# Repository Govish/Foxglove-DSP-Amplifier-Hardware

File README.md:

# Foxglove DSP Amplifier
 Design data for a DSP-based guitar effects processor

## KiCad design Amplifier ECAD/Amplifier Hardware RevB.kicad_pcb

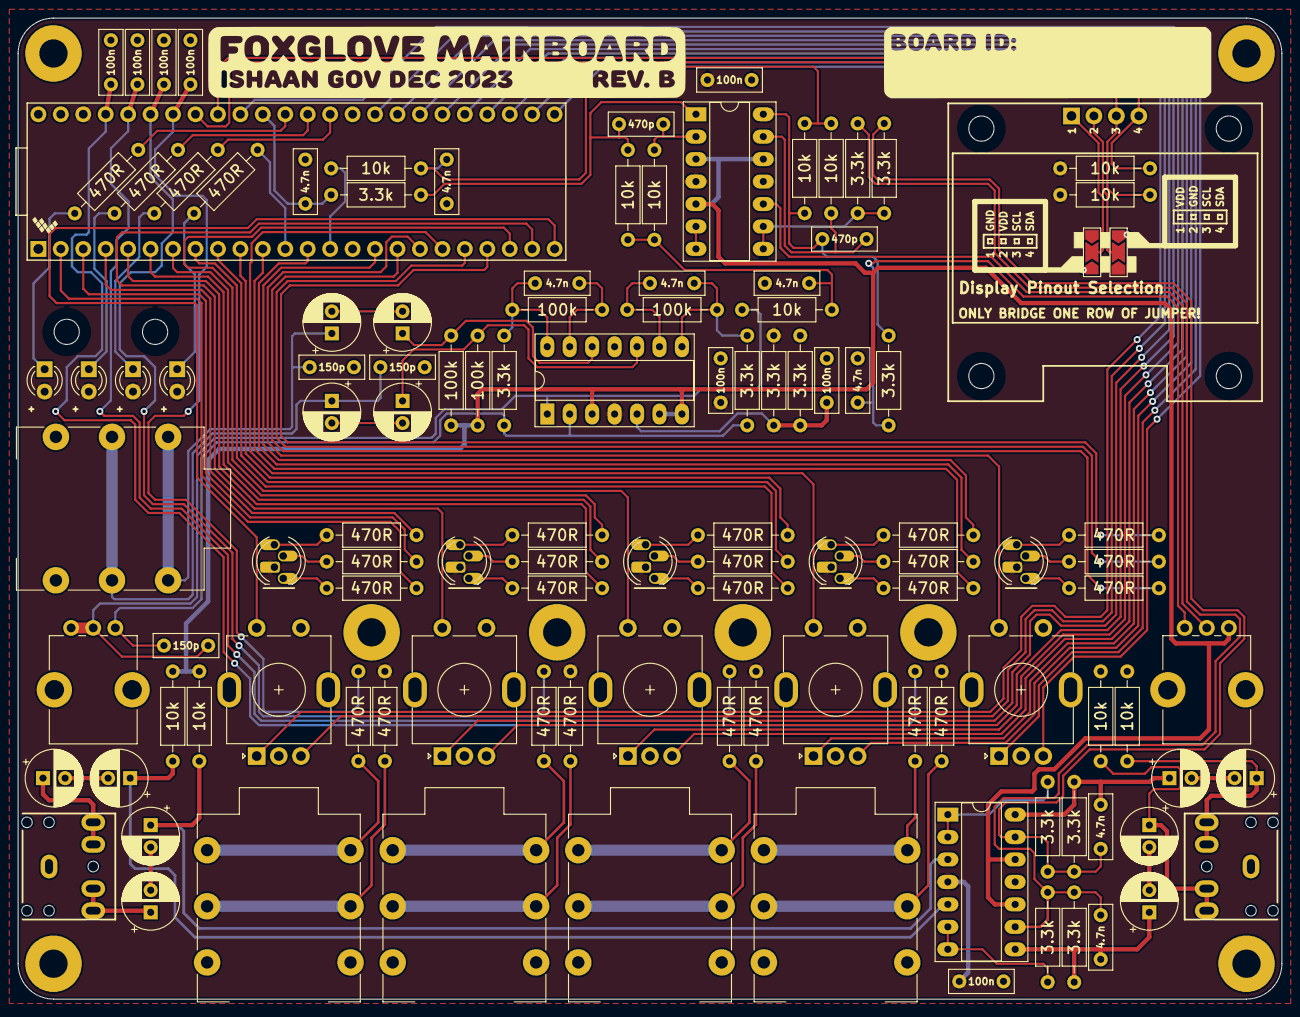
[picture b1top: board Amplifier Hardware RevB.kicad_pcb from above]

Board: 2 copper layers, 143.0 x 111.0 mm, 132 parts (0 on the bottom side), 113 nets.

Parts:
C1, C2, C3, C4, C7, C8, C9, C10, C16, C17, C18, C19: 100u; CP_KEMET_ESY
C5, C6, C13: 150p; C_KEMET_C317
C11, C12, C14, C15, C20, C22, C23, C25: 4.7n; C_KEMET_C322
C21, C24: 470p; C_KEMET_C317
C26, C27, C28, C29, C30, C31, C32, C33: 100n; C_KEMET_C317
D1, D2, D3, D4, D9: RGB; LED_D5.0mm-4_RGB
D5: RED; LED_D3.0mm_Clear
D6, D7, D8: YELLOW; LED_D3.0mm_Clear
H1, H2, H3, H4, H5, H6, H7, H8: M3; MountingHole_3.2mm_M3_Pad
H9, H10, H11, H12, H13, H14: M2.6; MountingHole_2.9mm_5.5mm_Ring
J1, J7: 3.5mm TRS; PJ-307
J2, J3, J4, J5, J6: NMJ6HFD2; Jack_6.35mm_Neutrik_NMJ6HFD2_Horizontal
JP1, JP2: SolderJumper_3_Bridged12; SolderJumper-3_P2.0mm_Open_TrianglePad1.0x1.5mm
R1, R2, R15, R16, R17, R18, R19, R21, R22, R23, R54, R55: 10k; R_Axial_DIN0207_L6.3mm_D2.5mm_P10.16mm_Horizontal
R3, R4, R5, R6: 100k; R_Axial_DIN0207_L6.3mm_D2.5mm_P10.16mm_Horizontal
R7, R8, R9, R10, R11, R12, R13, R14, R20, R24, R25, R26: 3.3k; R_Axial_DIN0207_L6.3mm_D2.5mm_P10.16mm_Horizontal
R27, R28, R29, R30, R31, R32, R33, R34, R35, R36, R37, R38, R39, R40, R41, R42, R43, R44, R45, R46, R47, R48, R49, R50, R51, R52, R53: 470R; R_Axial_DIN0207_L6.3mm_D2.5mm_P10.16mm_Horizontal
RV1, RV2: 100k Log; Potentiometer_Bourns_PTV09A-1_Single_Vertical
SW1, SW2, SW3, SW4, SW5: EC11; RotaryEncoder_Alps_EC11E-Switch_Vertical_H20mm
U1, U2, U3: MCP6004; DIP-14_W7.62mm_Socket_LongPads_IC
U4: Teensy 4.1; Teensy_4_1_Basic_Socket
U5: SH1106; SH1106_LCD_MODULE

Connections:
+3.3V: C26.1, C28.1, C29.1, D1.2 (A), D2.2 (A), D3.2 (A), D4.2 (A), D5.2 (A), D6.2 (A), D7.2 (A), D8.2 (A), D9.2 (A), JP1.1 (A), JP2.3 (B), R25.2, R30.1, R35.1, R40.1, R45.1, R54.1, R55.1, U1.4 (V+), U2.4 (V+), U3.4 (V+), U4.46 (3V3)
/Anti-Aliasing Filter/AMP_INST_IN: C13.2, R17.1, RV1.2, RV1.3, U1.1
/Anti-Aliasing Filter/FILT_INST_IN: C22.1, R20.2, U4.38 ((A2)PIN_16)
/BIAS: R1.1, R2.1, R3.1, R4.1, RV2.1, U1.3 (+), U1.6 (-), U1.7, U2.10 (+), U2.12 (+), U3.3 (+), U3.5 (+), U3.12 (+)
/Effect Channel 1/ENC_A: SW1.A, U4.25 (~PIN_33)
/Effect Channel 1/ENC_B: SW1.B, U4.26 (PIN_34)
/Effect Channel 1/ENC_SW: SW1.S2, U4.24 (PIN_32)
/Effect Channel 1/EXP_IN: C30.1, R31.1, U4.42 ((A6)PIN_20)
/Effect Channel 1/EXP_PWR: J3.R, J3.RN, R30.2
/Effect Channel 1/EXP_SIG: J3.T, J3.TN, R31.2
/Effect Channel 1/LED_B: R29.1, U4.3 (~PIN_1)
/Effect Channel 1/LED_G: R28.1, U4.4 (~PIN_2)
/Effect Channel 1/LED_R: R27.1, U4.2 (~PIN_0)
/Effect Channel 2/ENC_A: SW2.A, U4.27 (PIN_35)
/Effect Channel 2/ENC_B: SW2.B, U4.28 (~PIN_36)
/Effect Channel 2/ENC_SW: SW2.S2, U4.23 (PIN_31)
/Effect Channel 2/EXP_IN: C31.1, R36.1, U4.43 ((A7)PIN_21)
/Effect Channel 2/EXP_PWR: J4.R, J4.RN, R35.2
/Effect Channel 2/EXP_SIG: J4.T, J4.TN, R36.2
/Effect Channel 2/LED_B: R34.1, U4.6 (~PIN_4)
/Effect Channel 2/LED_G: R33.1, U4.7 (~PIN_5)
/Effect Channel 2/LED_R: R32.1, U4.5 (~PIN_3)
/Effect Channel 3/ENC_A: SW3.A, U4.29 (~PIN_37)
/Effect Channel 3/ENC_B: SW3.B, U4.30 ((A14)PIN_38)
/Effect Channel 3/ENC_SW: SW3.S2, U4.22 (PIN_30)
/Effect Channel 3/EXP_IN: C32.1, R41.1, U4.44 ((A8)PIN_22)
/Effect Channel 3/EXP_PWR: J5.R, J5.RN, R40.2
/Effect Channel 3/EXP_SIG: J5.T, J5.TN, R41.2
/Effect Channel 3/LED_B: R39.1, U4.9 (~PIN_7)
/Effect Channel 3/LED_G: R38.1, U4.10 (~PIN_8)
/Effect Channel 3/LED_R: R37.1, U4.8 (~PIN_6)
/Effect Channel 4/ENC_A: SW4.A, U4.31 ((A15)PIN_39)
/Effect Channel 4/ENC_B: SW4.B, U4.32 ((A16)PIN_40)
/Effect Channel 4/ENC_SW: SW4.S2, U4.19 (PIN_27(A13))
/Effect Channel 4/EXP_IN: C33.1, R46.1, U4.45 ((A9)PIN_23)
/Effect Channel 4/EXP_PWR: J6.R, J6.RN, R45.2
/Effect Channel 4/EXP_SIG: J6.T, J6.TN, R46.2
/Effect Channel 4/LED_B: R44.1, U4.13 (~PIN_11)
/Effect Channel 4/LED_G: R43.1, U4.16 (~PIN_24(A10))
/Effect Channel 4/LED_R: R42.1, U4.11 (~PIN_9)
/Instrument In/INST_IN_L: C5.2, C7.1, J2.T, J2.TN
/Instrument In/INST_IN_R: C6.2, C8.1, J2.R, J2.RN
/Line In/BUF_LINE_IN_L: R9.1, U2.1, U2.2 (-)
/Line In/BUF_LINE_IN_R: R12.1, U2.6 (-), U2.7
/Line In/LINE_IN_L: C1.1, J1.T, J1.TN
/Line In/LINE_IN_R: C2.1, J1.R, J1.RN
/MCU/EFFECT_RAW: R21.1, U4.14 (~PIN_12)
/MCU/ENC_A_UI: SW5.A, U4.33 ((A17)PIN_41)
/MCU/ENC_B_UI: SW5.B, U4.39 ((A3)PIN_17)
/MCU/ENC_SW_UI: SW5.S2, U4.18 (PIN_26(A12))
/MCU/LED_B_UI: R49.1, U4.20 (~PIN_28)
/MCU/LED_G_UI: R48.1, U4.21 (~PIN_29)
/MCU/LED_R_UI: R47.1, U4.17 (~PIN_25(A11))
/MCU/LEVEL_0: R50.1, U4.37 (~(A1)PIN_15)
/MCU/LEVEL_1: R51.1, U4.36 (~(A0)PIN_14)
/MCU/LEVEL_2: R52.1, U4.35 (~PIN_13)
/MCU/LEVEL_3: R53.1, U4.12 (~PIN_10)
/MCU/SCL: R54.2, U4.41 ((A5)PIN_19), U5.3 (SCL)
/MCU/SDA: R55.2, U4.40 ((A4)PIN_18), U5.4 (SDA)
/Reconstruction Filter/EFFECT_RECON: C25.1, R24.2, RV2.3
/Volume_Mixing_Output/LINE_OUT_L: C18.1, J7.T, J7.TN, R15.2
/Volume_Mixing_Output/LINE_OUT_R: C19.1, J7.R, J7.RN, R16.2
GND: C5.1, C6.1, C20.2, C22.2, C23.2, C25.2, C26.2, C27.2, C28.2, C29.2, C30.2, C31.2, C32.2, C33.2, H1.1, H2.1, H3.1, H4.1, H5.1, H6.1, H7.1, H8.1, J1.S, J2.S, J2.SN, J3.S, J3.SN, J4.S, J4.SN, J5.S, J5.SN, J6.S, J6.SN, J7.S, JP1.3 (B), JP2.1 (A), R15.1, R16.1, R26.1, RV1.MNT, RV2.MNT, SW1.C, SW1.MP, SW1.S1, SW2.C, SW2.MP, SW2.S1, SW3.C, SW3.MP, SW3.S1, SW4.C, SW4.MP, SW4.S1, SW5.C, SW5.MP, SW5.S1, U1.11 (V-), U2.11 (V-), U3.11 (V-), U4.1 (GND), U4.34 (GND), U4.47 (GND)
unnamed: C1.2, C3.2
unnamed: C2.2, C4.2
unnamed: C7.2, C9.2
unnamed: C8.2, C10.2
unnamed: C11.2, R5.2, R7.1, U1.14
unnamed: C12.2, R6.2, R8.1, U1.8
unnamed: C14.2, C16.1, R13.2, U2.14
unnamed: C15.2, C17.1, R14.2, U2.8
unnamed: C16.2, C18.2
unnamed: C17.2, C19.2
unnamed: C20.1, R17.2, R18.1, R19.1
unnamed: C21.1, R18.2, R20.1, U3.1
unnamed: C23.1, R21.2, R22.1, R23.1
unnamed: C24.1, R22.2, R24.1, U3.14
unnamed: D1.3 (BK), R29.2
unnamed: D1.4 (GK), R28.2
unnamed: D1.1 (RK), R27.2
unnamed: D2.3 (BK), R34.2
unnamed: D2.4 (GK), R33.2
unnamed: D2.1 (RK), R32.2
unnamed: D3.3 (BK), R39.2
unnamed: D3.4 (GK), R38.2
unnamed: D3.1 (RK), R37.2
unnamed: D4.3 (BK), R44.2
unnamed: D4.4 (GK), R43.2
unnamed: D4.1 (RK), R42.2
unnamed: D5.1 (K), R50.2
unnamed: D6.1 (K), R51.2
unnamed: D7.1 (K), R52.2
unnamed: D8.1 (K), R53.2
unnamed: D9.3 (BK), R49.2
unnamed: D9.4 (GK), R48.2
unnamed: D9.1 (RK), R47.2
unnamed: JP1.2 (C), U5.1 (VDD)
unnamed: JP2.2 (C), U5.2 (GND)
unnamed: C13.1, R7.2, R8.2, RV1.1, U1.2 (-)
unnamed: C27.1, R25.1, R26.2, U1.5 (+)
unnamed: C10.1, R4.2, U1.10 (+)
unnamed: C12.1, R6.1, U1.9 (-)
unnamed: C9.1, R3.2, U1.12 (+)
unnamed: C11.1, R5.1, U1.13 (-)
unnamed: C3.1, R1.2, U2.3 (+)
unnamed: C4.1, R2.2, U2.5 (+)
unnamed: C15.1, R11.2, R12.2, R14.1, U2.9 (-)
unnamed: C14.1, R9.2, R10.2, R13.1, U2.13 (-)
unnamed: C21.2, R19.2, U3.2 (-)
unnamed: U3.6 (-), U3.7
unnamed: RV2.2, U3.10 (+)
unnamed: R10.1, R11.1, U3.8, U3.9 (-)
unnamed: C24.2, R23.2, U3.13 (-)

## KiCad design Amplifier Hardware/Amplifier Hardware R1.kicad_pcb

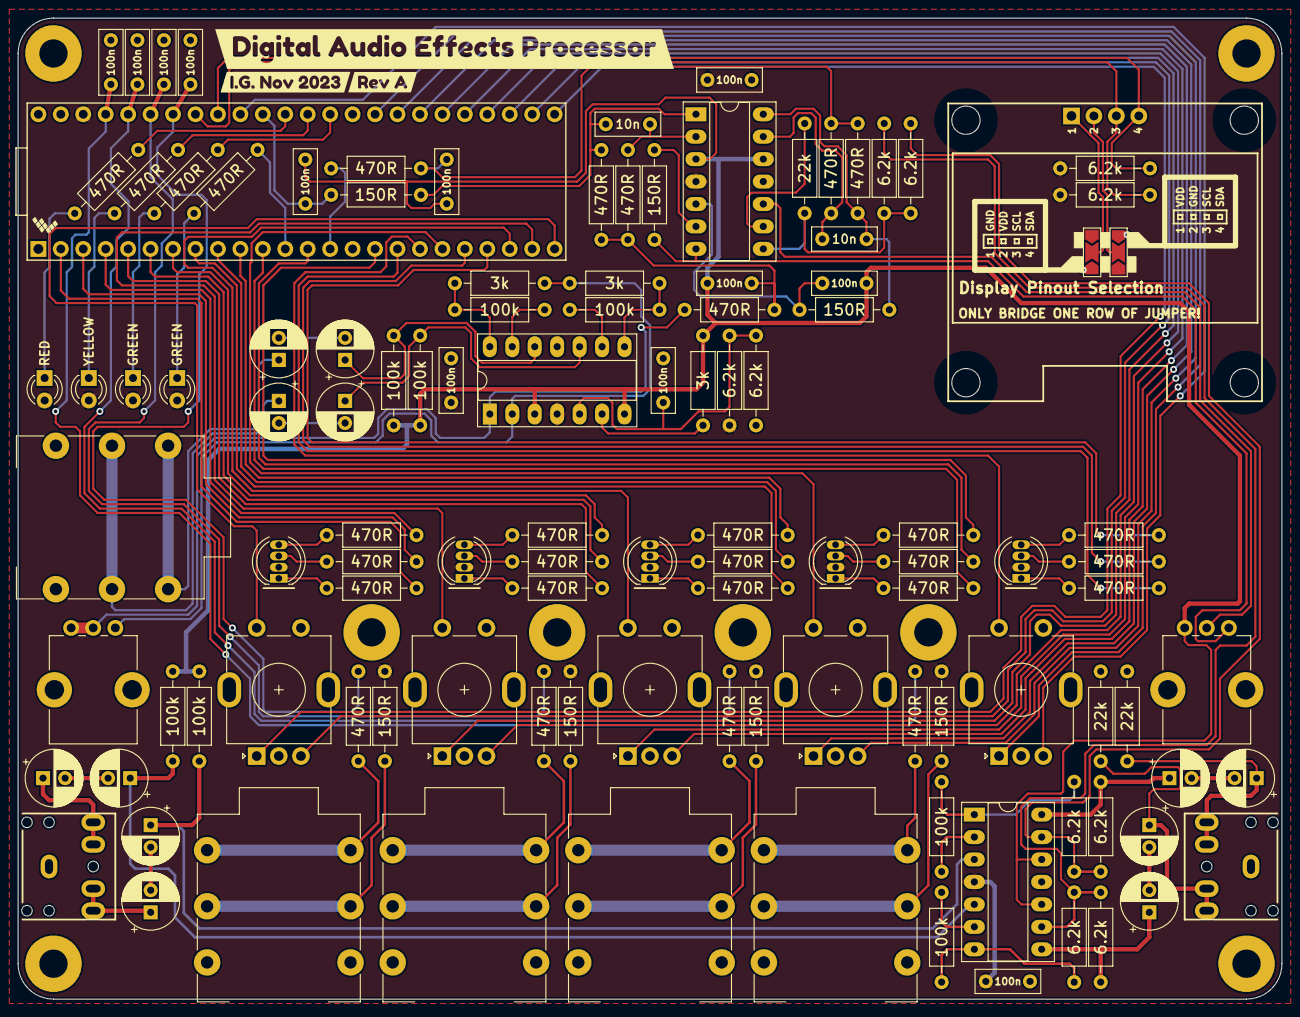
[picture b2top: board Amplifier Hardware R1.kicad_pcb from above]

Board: 2 copper layers, 143.0 x 111.0 mm, 127 parts (0 on the bottom side), 118 nets.

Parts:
C1, C2, C3, C4, C5, C6, C7, C8, C9, C10, C11, C12: 100u; CP_Radial_D6.3mm_H12.5_P2.50mm
C13, C15, C16, C18, C19, C20, C21, C22, C23, C24, C25, C26: 100n; C_Rect_L7.2mm_W2.5mm_H6.6mm_P5.00mm_MODIFIED
C14, C17: 10n; C_Rect_L7.2mm_W2.5mm_H6.6mm_P5.00mm_MODIFIED
D1, D2, D3, D4, D9: QBL8RGB60D0-2897; LED_D5.0mm-4_RGB
D5: RED; LED_D3.0mm_Clear
D6: YELLOW; LED_D3.0mm_Clear
D7, D8: GREEN; LED_D3.0mm_Clear
H1, H2, H3, H4, H5, H6, H7, H8: M3; MountingHole_3.2mm_M3_Pad
J1, J7: SJ1-3525N; PJ-307
J2, J3, J4, J5, J6: NMJ6HFD2; Jack_6.35mm_Neutrik_NMJ6HFD2_Horizontal
JP1, JP2: SolderJumper_3_Bridged12; SolderJumper-3_P2.0mm_Open_TrianglePad1.0x1.5mm
R1, R2, R3, R4, R15, R16, R17, R18: 100k; R_Axial_DIN0207_L6.3mm_D2.5mm_P10.16mm_Horizontal
R5, R24, R28, R35, R40, R45, R50: 150R; R_Axial_DIN0207_L6.3mm_D2.5mm_P10.16mm_Horizontal
R6, R13, R14: 22k; R_Axial_DIN0207_L6.3mm_D2.5mm_P10.16mm_Horizontal
R7, R8, R9, R10, R11, R12, R29, R30, R59, R60: 6k2; R_Axial_DIN0207_L6.3mm_D2.5mm_P10.16mm_Horizontal
R19, R20, R31: 3k; R_Axial_DIN0207_L6.3mm_D2.5mm_P10.16mm_Horizontal
R21, R22, R23, R25, R26, R27, R32, R33, R34, R36, R37, R38, R39, R41, R42, R43, R44, R46, R47, R48, R49, R51, R52, R53, R54, R55, R56, R57, R58: 470R; R_Axial_DIN0207_L6.3mm_D2.5mm_P10.16mm_Horizontal
RV1, RV2: 100k Log; Potentiometer_Bourns_PTV09A-1_Single_Vertical
SW1, SW2, SW3, SW4, SW5: EC11; RotaryEncoder_Alps_EC11E-Switch_Vertical_H20mm
U1, U2, U3: MCP6004; DIP-14_W7.62mm_Socket_LongPads_IC
U4: Teensy 4.1; Teensy_4_1_Basic_Socket
U5: SH1106; SH1106_LCD_MODULE
kibuzzard-6562A21D: G***; kibuzzard-6562A21D
kibuzzard-6562A25D: G***; kibuzzard-6562A25D
kibuzzard-6562EE33: G***; kibuzzard-6562EE33

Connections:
+3.3V: C19.1, C21.1, C22.1, D1.2 (A), D2.2 (A), D3.2 (A), D4.2 (A), D5.2 (A), D6.2 (A), D7.2 (A), D8.2 (A), D9.2 (A), JP1.1 (A), JP2.3 (B), R29.1, R35.1, R40.1, R45.1, R50.1, R59.2, R60.2, U1.4 (V+), U2.4 (V+), U3.4 (V+), U4.46 (3V3)
/Anti-Aliasing Filter/AMP_INST_IN: R21.1, RV2.2, RV2.3, U3.1
/Anti-Aliasing Filter/FILT_INST_IN: C15.1, R24.2, U4.38 ((A2)PIN_16)
/BIAS: C13.2, C15.2, C16.2, C18.2, R1.1, R2.1, R15.1, R16.1, R31.2, RV1.3, U1.10 (+), U1.12 (+), U2.3 (+), U2.12 (+), U3.3 (+), U3.7
/Effect Channel 1/ENC_A: SW4.A, U4.25 (~PIN_33)
/Effect Channel 1/ENC_B: SW4.B, U4.26 (PIN_34)
/Effect Channel 1/ENC_SW: SW4.S2, U4.24 (PIN_32)
/Effect Channel 1/EXP_IN: C26.1, R51.1, U4.42 ((A6)PIN_20)
/Effect Channel 1/EXP_PWR: J3.R, J3.RN, R50.2
/Effect Channel 1/EXP_SIG: J3.T, J3.TN, R51.2
/Effect Channel 1/LED_B: R49.1, U4.3 (~PIN_1)
/Effect Channel 1/LED_G: R48.1, U4.4 (~PIN_2)
/Effect Channel 1/LED_R: R47.1, U4.2 (~PIN_0)
/Effect Channel 2/ENC_A: SW2.A, U4.27 (PIN_35)
/Effect Channel 2/ENC_B: SW2.B, U4.28 (~PIN_36)
/Effect Channel 2/ENC_SW: SW2.S2, U4.23 (PIN_31)
/Effect Channel 2/EXP_IN: C24.1, R41.1, U4.43 ((A7)PIN_21)
/Effect Channel 2/EXP_PWR: J4.R, J4.RN, R40.2
/Effect Channel 2/EXP_SIG: J4.T, J4.TN, R41.2
/Effect Channel 2/LED_B: R39.1, U4.6 (~PIN_4)
/Effect Channel 2/LED_G: R38.1, U4.7 (~PIN_5)
/Effect Channel 2/LED_R: R37.1, U4.5 (~PIN_3)
/Effect Channel 3/ENC_A: SW1.A, U4.29 (~PIN_37)
/Effect Channel 3/ENC_B: SW1.B, U4.30 ((A14)PIN_38)
/Effect Channel 3/ENC_SW: SW1.S2, U4.22 (PIN_30)
/Effect Channel 3/EXP_IN: C23.1, R36.1, U4.44 ((A8)PIN_22)
/Effect Channel 3/EXP_PWR: J5.R, J5.RN, R35.2
/Effect Channel 3/EXP_SIG: J5.T, J5.TN, R36.2
/Effect Channel 3/LED_B: R34.1, U4.9 (~PIN_7)
/Effect Channel 3/LED_G: R33.1, U4.10 (~PIN_8)
/Effect Channel 3/LED_R: R32.1, U4.8 (~PIN_6)
/Effect Channel 4/ENC_A: SW3.A, U4.31 ((A15)PIN_39)
/Effect Channel 4/ENC_B: SW3.B, U4.32 ((A16)PIN_40)
/Effect Channel 4/ENC_SW: SW3.S2, U4.19 (PIN_27(A13))
/Effect Channel 4/EXP_IN: C25.1, R46.1, U4.45 ((A9)PIN_23)
/Effect Channel 4/EXP_PWR: J6.R, J6.RN, R45.2
/Effect Channel 4/EXP_SIG: J6.T, J6.TN, R46.2
/Effect Channel 4/LED_B: R44.1, U4.13 (~PIN_11)
/Effect Channel 4/LED_G: R43.1, U4.16 (~PIN_24(A10))
/Effect Channel 4/LED_R: R42.1, U4.11 (~PIN_9)
/Instrument In/INST_IN_L: C9.1, J2.T, J2.TN
/Instrument In/INST_IN_R: C10.1, J2.R, J2.RN
/Line In/BUF_LINE_IN_L: R3.2, R8.1, U1.1
/Line In/BUF_LINE_IN_R: R4.2, R10.1, U1.7
/Line In/LINE_IN_L: C1.1, J1.T, J1.TN
/Line In/LINE_IN_R: C2.1, J1.R, J1.RN
/MCU/EFFECT_RAW: R25.1, U4.14 (~PIN_12)
/MCU/ENC_A_UI: SW5.A, U4.33 ((A17)PIN_41)
/MCU/ENC_B_UI: SW5.B, U4.39 ((A3)PIN_17)
/MCU/ENC_SW_UI: SW5.S2, U4.18 (PIN_26(A12))
/MCU/LED_B_UI: R54.1, U4.20 (~PIN_28)
/MCU/LED_G_UI: R53.1, U4.21 (~PIN_29)
/MCU/LED_R_UI: R52.1, U4.17 (~PIN_25(A11))
/MCU/LEVEL_0: R55.1, U4.37 (~(A1)PIN_15)
/MCU/LEVEL_1: R56.1, U4.36 (~(A0)PIN_14)
/MCU/LEVEL_2: R57.1, U4.35 (~PIN_13)
/MCU/LEVEL_3: R58.1, U4.12 (~PIN_10)
/MCU/SCL: R59.1, U4.41 ((A5)PIN_19), U5.3 (SCL)
/MCU/SDA: R60.1, U4.40 ((A4)PIN_18), U5.4 (SDA)
/Reconstruction Filter/EFFECT_RECON: C18.1, R28.2, U2.5 (+)
/Volume_Mixing_Output/LINE_OUT_L: C7.1, J7.T, J7.TN, R13.2
/Volume_Mixing_Output/LINE_OUT_R: C8.1, J7.R, J7.RN, R14.2
GND: C19.2, C20.2, C21.2, C22.2, C23.2, C24.2, C25.2, C26.2, H1.1, H2.1, H3.1, H4.1, H5.1, H6.1, H7.1, H8.1, J1.S, J2.S, J2.SN, J3.S, J3.SN, J4.S, J4.SN, J5.S, J5.SN, J6.S, J6.SN, J7.S, JP1.3 (B), JP2.1 (A), R13.1, R14.1, R30.2, RV1.MNT, RV2.MNT, SW1.C, SW1.MP, SW1.S1, SW2.C, SW2.MP, SW2.S1, SW3.C, SW3.MP, SW3.S1, SW4.C, SW4.MP, SW4.S1, SW5.C, SW5.MP, SW5.S1, U1.11 (V-), U2.11 (V-), U3.11 (V-), U4.1 (GND), U4.34 (GND), U4.47 (GND)
unnamed: C1.2, C3.2
unnamed: C2.2, C4.2
unnamed: C5.1, R11.2, U1.14
unnamed: C5.2, C7.2
unnamed: C6.1, R12.2, U1.8
unnamed: C6.2, C8.2
unnamed: C10.2, C12.2
unnamed: C9.2, C11.2
unnamed: C13.1, R21.2, R22.1, R23.1
unnamed: C14.1, R22.2, R24.1, U2.1
unnamed: C16.1, R25.2, R26.1, R27.1
unnamed: C17.1, R26.2, R28.1, U2.14
unnamed: D1.3 (BK), R34.2
unnamed: D1.4 (GK), R33.2
unnamed: D1.1 (RK), R32.2
unnamed: D2.3 (BK), R39.2
unnamed: D2.4 (GK), R38.2
unnamed: D2.1 (RK), R37.2
unnamed: D3.3 (BK), R44.2
unnamed: D3.4 (GK), R43.2
unnamed: D3.1 (RK), R42.2
unnamed: D4.3 (BK), R49.2
unnamed: D4.4 (GK), R48.2
unnamed: D4.1 (RK), R47.2
unnamed: D5.1 (K), R55.2
unnamed: D6.1 (K), R56.2
unnamed: D7.1 (K), R57.2
unnamed: D8.1 (K), R58.2
unnamed: D9.3 (BK), R54.2
unnamed: D9.4 (GK), R53.2
unnamed: D9.1 (RK), R52.2
unnamed: JP1.2 (C), U5.1 (VDD)
unnamed: JP2.2 (C), U5.2 (GND)
unnamed: R5.2, RV1.1, U2.7
unnamed: R6.2, R7.1, R9.1, U2.8
unnamed: R17.2, R19.1, U3.14
unnamed: R18.2, R20.1, U3.8
unnamed: C3.1, R1.2, U1.3 (+)
unnamed: R3.1, U1.2 (-)
unnamed: C4.1, R2.2, U1.5 (+)
unnamed: R4.1, U1.6 (-)
unnamed: R9.2, R10.2, R12.1, U1.9 (-)
unnamed: R7.2, R8.2, R11.1, U1.13 (-)
unnamed: C14.2, R23.2, U2.2 (-)
unnamed: R5.1, U2.6 (-)
unnamed: RV1.2, U2.10 (+)
unnamed: R6.1, U2.9 (-)
unnamed: C17.2, R27.2, U2.13 (-)
unnamed: R19.2, R20.2, RV2.1, U3.2 (-)
unnamed: C20.1, R29.2, R30.1, U3.5 (+)
unnamed: R31.1, U3.6 (-)
unnamed: C12.1, R16.2, U3.10 (+)
unnamed: R18.1, U3.9 (-)
unnamed: C11.1, R15.2, U3.12 (+)
unnamed: R17.1, U3.13 (-)

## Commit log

2023-11-26 First commit! Publishing first revision of the design
2023-12-15 Pushing some updates for the second revision of the board
2023-12-15 Solid polygon connections for holes
2023-12-15 File renaming; updating supplier references
2023-12-19 Test firmware for Foxglove
2023-12-22 Audio passthrough working!!!!!!
2023-12-25 Front and rear panel work; renderings on Fusion360
2023-12-28 Firmware work--RGB LEDs, Encoders, Scheduler
2024-01-09 lotsa UI work, still some issues with draw menu, parameter rendering hasn't been implemented yet
2024-01-11 Complete UI Code! Minus quick-edit parameters
2024-01-17 IIR Lowpass, Minor effect encoder initialization bugfix
2024-01-22 Idle screen for noise reduction
2024-01-23 Removing firmware from the repo
2024-01-23 Explicitly demarcating Rev A Hardware
